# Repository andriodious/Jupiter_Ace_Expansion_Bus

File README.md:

# Jupiter_Ace_Expansion_Bus
Provides a selection of Adapter boards for Jupiter Ace Bus Expansion

Created in KiCAD with Gerber files included.

There are 3 discrete boards in this repository:

* Ace to 50-Way - Adapts the Jupiter Ace external expansion bus to a 50-Way IDC header. 

* 50-Way to Ace - Adapts the 50-Way IDC header back an Ace-Bus format for legacy expansion peripherals

* Buffered 50-Way - Buffers address, data, clock and selected control lines with external input on Pin 50 'BufDir'. The BufDir signal is intended to be driven low by any given external device select signal. Each select signal must be connected via a logic IC, or schottky diode e.g. BAT85, to the BufDir input. Decoding of the select signals is expected to be 'one-hot' and handled by the expansion peripheral(s). This will allow the buffered interface board to correctly set the direction of the read data signals.

Note the conventional 50-way header pinout is 'reversed' on this design such that pin 1 corresponds to the leftmost pins on the IDC header, this was a concious choice in order to create more of a 1:1 connection with the Ace Bus.

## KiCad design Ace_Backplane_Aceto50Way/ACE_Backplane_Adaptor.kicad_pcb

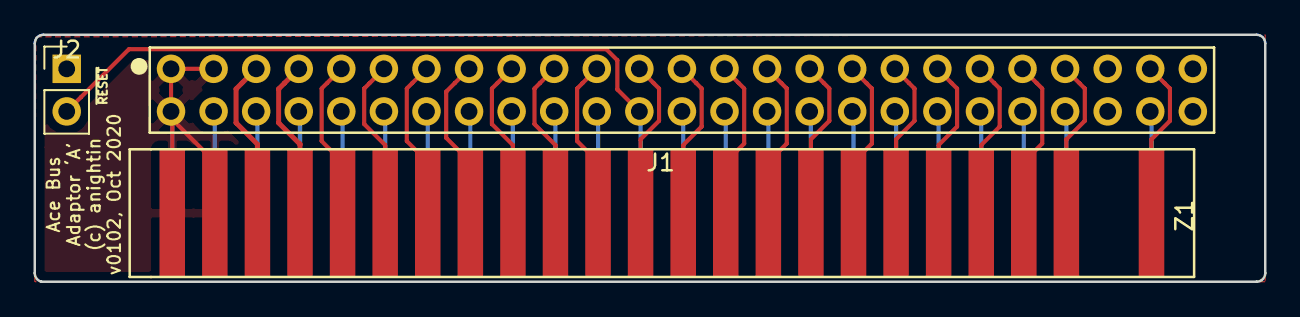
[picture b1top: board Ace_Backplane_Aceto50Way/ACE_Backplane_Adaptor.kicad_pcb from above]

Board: 2 copper layers, 73.4 x 14.7 mm, 3 parts (0 on the bottom side), 44 nets.

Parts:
J1: AceBUS_Pin_Header; Ace_Bus_Pin_Header
J2: ~RESET_SW; PinHeader_1x02_P2.54mm_Vertical
Z1: AceBUS; Ace_Bus_Edge_Connector

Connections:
GND: J1.A1, J1.A2, J1.B1, J2.1, Z1.A1, Z1.A2, Z1.B1
unnamed: J1.A3, Z1.A3
unnamed: J1.A4, Z1.A4
unnamed: J1.A5, Z1.A5
unnamed: J1.A6, Z1.A6
unnamed: J1.A7, Z1.A7
unnamed: J1.A8, Z1.A8
unnamed: J1.A9, Z1.A9
unnamed: J1.A10, Z1.A10
unnamed: J1.A11, Z1.A11
unnamed: J1.A12, Z1.A12
unnamed: J1.A13, Z1.A13
unnamed: J1.A14, Z1.A14
unnamed: J1.A15, Z1.A15
unnamed: J1.A16, Z1.A16
unnamed: J1.A17, Z1.A17
unnamed: J1.A18, Z1.A18
unnamed: J1.A19, Z1.A19
unnamed: J1.A20, Z1.A20
unnamed: J1.A21, Z1.A21
unnamed: J1.A22, Z1.A22
unnamed: J1.A24, Z1.A24
unnamed: J1.B2, Z1.B2
unnamed: J1.B3, Z1.B3
unnamed: J1.B4, Z1.B4
unnamed: J1.B5, Z1.B5
unnamed: J1.B6, Z1.B6
unnamed: J1.B7, Z1.B7
unnamed: J1.B8, Z1.B8
unnamed: J1.B9, Z1.B9
unnamed: J1.B10, Z1.B10
unnamed: J1.B11, Z1.B11
unnamed: J1.B12, J2.2, Z1.B12
unnamed: J1.B13, Z1.B13
unnamed: J1.B14, Z1.B14
unnamed: J1.B15, Z1.B15
unnamed: J1.B16, Z1.B16
unnamed: J1.B17, Z1.B17
unnamed: J1.B18, Z1.B18
unnamed: J1.B19, Z1.B19
unnamed: J1.B20, Z1.B20
unnamed: J1.B21, Z1.B21
unnamed: J1.B22, Z1.B22
unnamed: J1.B24, Z1.B24

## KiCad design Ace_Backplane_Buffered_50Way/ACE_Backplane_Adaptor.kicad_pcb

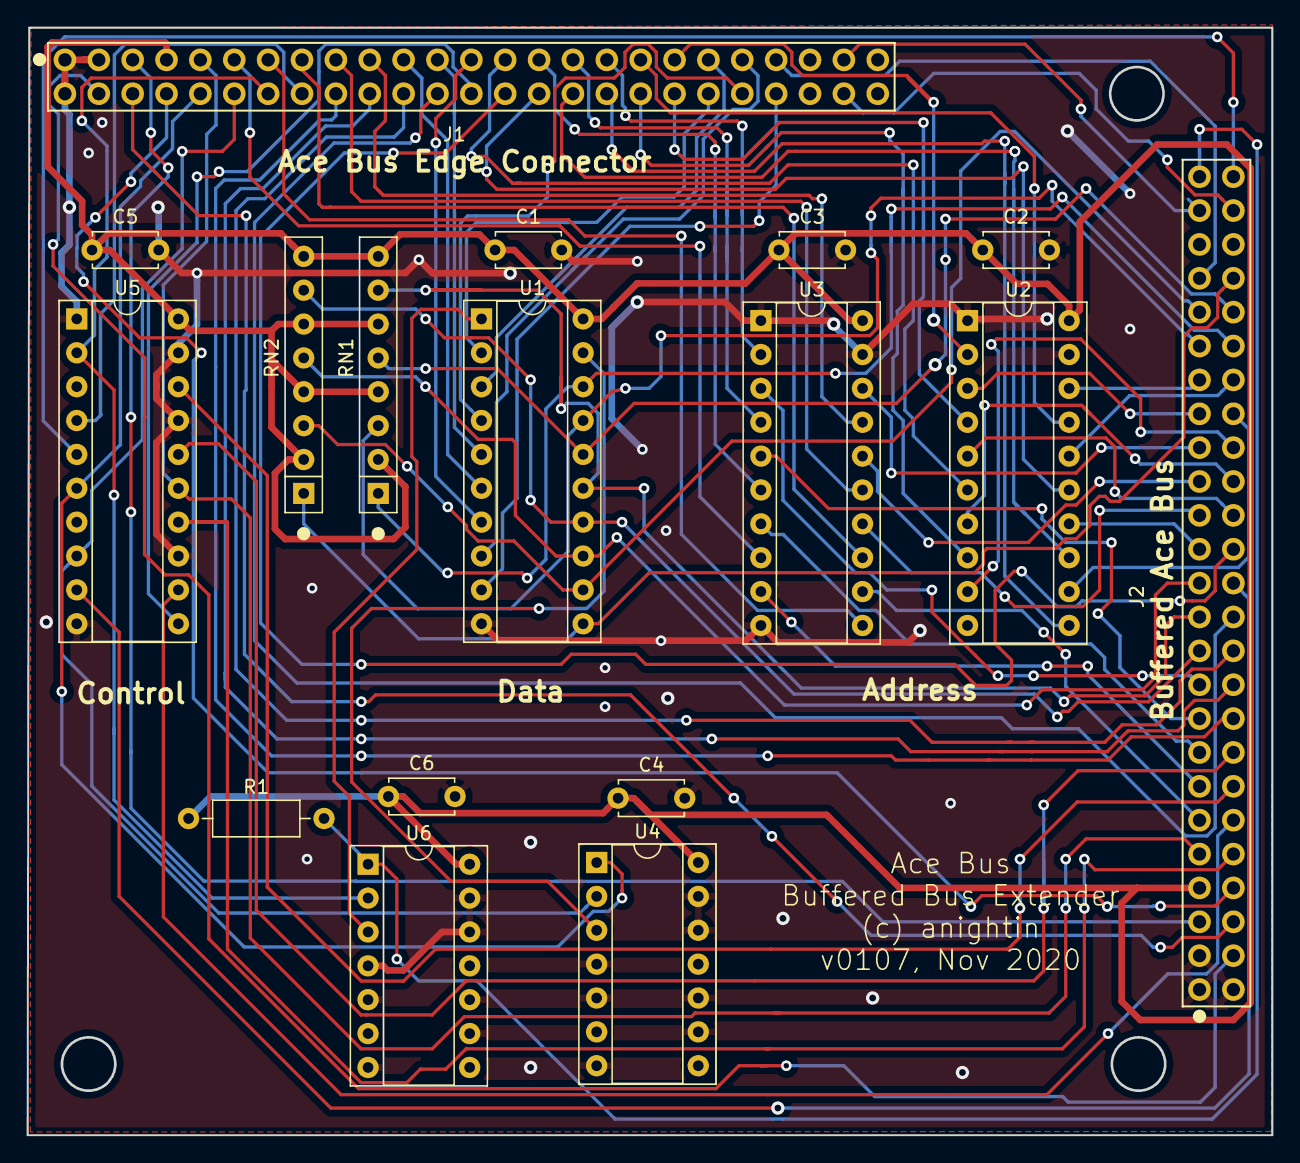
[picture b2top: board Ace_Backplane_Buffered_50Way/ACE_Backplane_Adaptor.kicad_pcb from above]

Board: 2 copper layers, 93.3 x 83.1 mm, 17 parts (0 on the bottom side), 77 nets.

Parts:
C1, C2, C3, C4, C5, C6: 100n; C_Disc_D4.7mm_W2.5mm_P5.00mm
J1, J2: AceBUS_Pin_Header; Ace_Bus_Pin_Header
R1: 1K; R_Axial_DIN0207_L6.3mm_D2.5mm_P10.16mm_Horizontal
RN1, RN2: 4K7; R_Array_SIP8
U1: 74LS245; DIP-20_W7.62mm_Socket
U2, U3, U5: 74LS244; DIP-20_W7.62mm_Socket
U4: 74LS08; DIP-14_W7.62mm_Socket
U6: 74LS32; DIP-14_W7.62mm_Socket

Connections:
/+9V: J1.A3, J2.A3
/-: J1.A24, J2.A24
/A0: J1.A19, U2.2
/A0': J2.A19, U2.18
/A1: J1.B19, U2.4
/A1': J2.B19, U2.16
/A2: J1.A14, U2.6
/A2': J2.A14, U2.14
/A3: J1.B18, U2.8
/A3': J2.B18, U2.12
/A4: J1.B17, U2.11
/A4': J2.B17, U2.9
/A5: J1.B16, U2.13
/A5': J2.B16, U2.7
/A6: J1.B15, U2.15
/A6': J2.B15, U2.5
/A7: J1.A18, U2.17
/A7': J2.A18, U2.3
/A8: J1.A17, U3.2
/A8': J2.A17, U3.18
/A9: J1.A16, U3.4
/A9': J2.A16, U3.16
/A10: J1.A15, U3.6
/A10': J2.A15, U3.14
/A11: J1.A6, U3.8
/A11': J2.A6, U3.12
/A12: J1.A7, U3.11
/A12': J2.A7, U3.9
/A13: J1.A8, U3.13
/A13': J2.A8, U3.7
/A14: J1.A9, U3.15
/A14': J2.A9, U3.5
/A15: J1.A10, U3.17
/A15': J2.A10, U3.3
/BufDir: U1.1, U6.3
/CLK: J1.A5, J2.A5, U5.15
/CLK': J2.B25, U5.5
/D0: J1.B20, U1.2
/D0': J2.B20, RN1.1, U1.18
/D1: J1.A20, U1.3
/D1': J2.A20, RN1.3, U1.17
/D2: J1.B21, U1.4
/D2': J2.B21, RN1.5, U1.16
/D3: J1.A12, U1.5
/D3': J2.A12, RN1.7, U1.15
/D4: J1.A11, U1.6
/D4': J2.A11, RN2.7, U1.14
/D5: J1.A13, U1.7
/D5': J2.A13, RN2.5, U1.13
/D6: J1.A21, U1.8
/D6': J2.A21, RN2.3, U1.12
/D7: J1.B22, U1.9
/D7': J2.B22, RN2.1, U1.11
/ExtDir: J2.A25, R1.2, U6.1
/SysRD: U1.19, U4.3
/~ACEROMCS: J1.B24, J2.B24
/~BUSACK: J1.B9, J2.B9
/~BUSREQ: J1.B11, J2.B11
/~HALT: J1.B4, J2.B4
/~INT: J1.B2, J2.B2
/~IORQ: J1.B6, U4.2, U5.8
/~IORQ': J2.B6, U5.12
/~M1: J1.B13, U5.11
/~M1': J2.B13, U5.9
/~MREQ: J1.B5, U4.1, U5.6
/~MREQ': J2.B5, U5.14
/~NMI: J1.B3, J2.B3
/~RD: J1.B7, U5.2, U6.2
/~RD': J2.B7, U5.18
/~RESET: J1.B12, J2.B12
/~RFSH: J1.B14, J2.B14
/~WAIT: J1.B10, J2.B10
/~WE: J1.A22, J2.A22
/~WR: J1.B8, U5.4
/~WR': J2.B8, U5.16
GND: C1.2, C2.2, C3.2, C4.2, C5.2, C6.2, J1.A1, J1.A2, J1.B1, J2.A1, J2.A2, J2.B1, U1.10, U2.1, U2.10, U2.19, U3.1, U3.10, U3.19, U4.4, U4.5, U4.7, U4.9, U4.10, U4.12, U4.13, U5.1, U5.10, U5.13, U5.17, U5.19, U6.4, U6.5, U6.7, U6.9, U6.10, U6.12, U6.13
VCC: C1.1, C2.1, C3.1, C4.1, C5.1, C6.1, J1.A4, J2.A4, R1.1, RN1.2, RN1.4, RN1.6, RN1.8, RN2.2, RN2.4, RN2.6, RN2.8, U1.20, U2.20, U3.20, U4.14, U5.20, U6.14

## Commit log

2020-10-31 Update LICENSE
